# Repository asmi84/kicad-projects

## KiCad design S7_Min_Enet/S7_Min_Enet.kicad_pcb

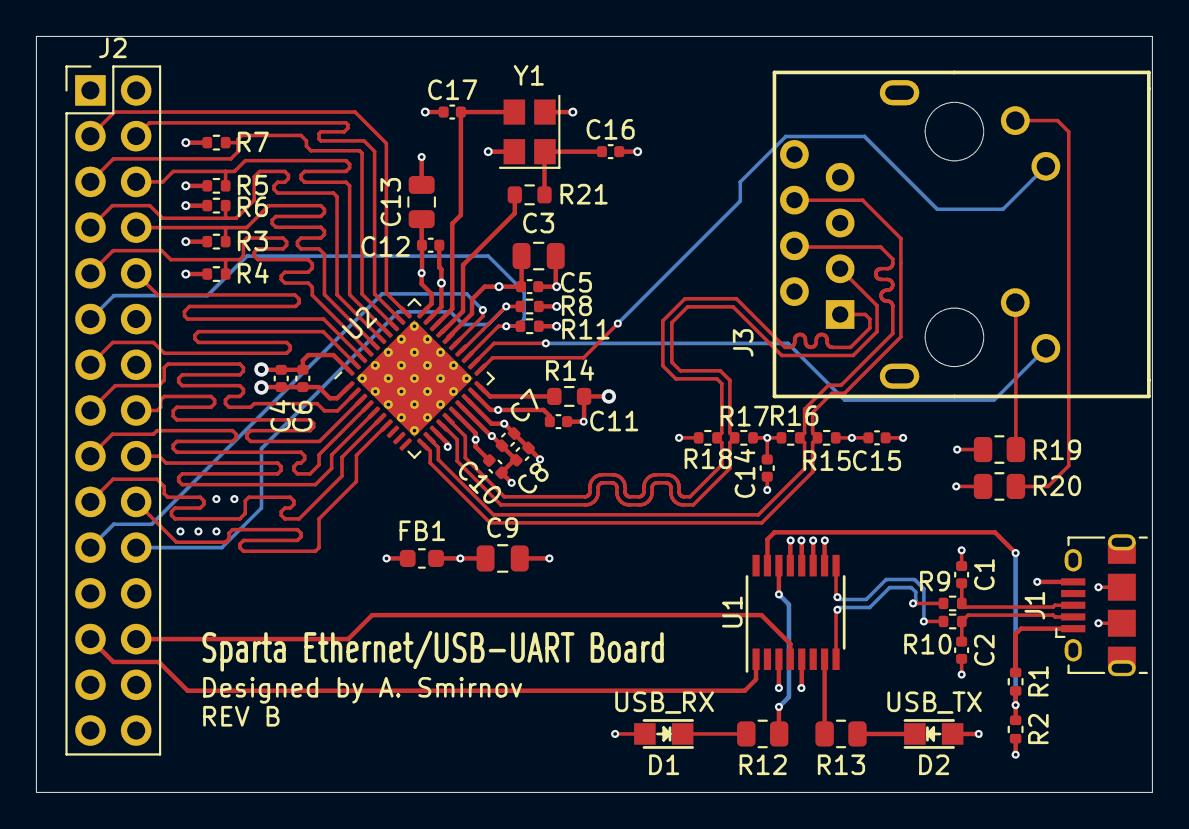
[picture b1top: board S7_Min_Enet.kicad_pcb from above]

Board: 4 copper layers, 62.0 x 42.0 mm, 47 parts (0 on the bottom side), 46 nets.

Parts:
C1, C2: 47pF; C_0402_1005Metric
C3, C9, C13: 10uF; C_0805_2012Metric
C4, C8: 1uF; C_0402_1005Metric
C5, C6, C7, C10, C11, C12, C14, C15: 0.1uF; C_0402_1005Metric
C16, C17: 33pF; C_0402_1005Metric
D1: USB_RX; LED_0805
D2: USB_TX; LED_0805
FB1: 600R; L_0603_1608Metric
J1: USB_B_Micro; USB_Micro-B_Amphenol_10118194_Horizontal
J2: Conn_02x15_Odd_Even; PinHeader_2x15_P2.54mm_Vertical
J3: J1B1211CCD
R1: 4.75K; R_0402_1005Metric
R2: 10K; R_0402_1005Metric
R3, R4, R5, R6: DNP; R_0402_1005Metric
R7, R8, R11: 2.2K; R_0402_1005Metric
R9, R10: 27; R_0402_1005Metric
R12, R13: 680; R_0805_2012Metric
R14: 4.87K; R_0603_1608Metric
R15, R16, R17, R18: 49.9; R_0402_1005Metric
R19, R20: 330; R_0805_2012Metric
R21: 0; R_0603_1608Metric
U1: FT230XS; SSOP-16_3.9x4.9mm_P0.635mm
U2: DP83848J; QFN-40-1EP_6x6mm_P0.5mm_EP4.6x4.6mm_ThermalVias
Y1: 25MHz; Crystal_SMD_3225-4Pin_3.2x2.5mm

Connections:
+3.3VA: C7.1, C8.1, C9.1, C14.1, C15.1, FB1.1, J3.2, J3.5, R15.2, R16.2, R17.2, R18.2, R19.1, R20.1, U2.18
+3V3: C3.1, C4.1, C5.1, C6.1, D1.2, D2.2, FB1.2, J2.1, J2.27, R3.2, R4.2, R5.2, R6.2, R7.2, R8.2, R11.2, U1.3, U1.10, U1.11, U1.12, U2.1, U2.26
/ETH_COL: J2.7, R6.1, U2.35
/ETH_CRS: J2.5, R7.1, U2.33
/ETH_MDC: J2.21, U2.25
/ETH_MDIO: J2.22, R8.1, U2.24
/ETH_RX+: J3.4, R16.1, U2.12
/ETH_RX-: J3.6, R15.1, U2.11
/ETH_RXD0: J2.8, R3.1, U2.36
/ETH_RXD1: J2.9, R4.1, U2.37
/ETH_RXD2: J2.10, U2.38
/ETH_RXD3: J2.13, U2.39
/ETH_RXERR: J2.6, R5.1, U2.34
/ETH_RX_CLK: J2.3, U2.31
/ETH_RX_DV: J2.4, U2.32
/ETH_TX+: J3.1, R18.1, U2.15
/ETH_TX-: J3.3, R17.1, U2.14
/ETH_TXD0: J2.17, U2.4
/ETH_TXD1: J2.18, U2.5
/ETH_TXD2: J2.19, U2.6
/ETH_TXD3: J2.20, U2.7
/ETH_TX_CLK: J2.15, U2.2
/ETH_TX_EN: J2.16, U2.3
/ETH_X1: C17.1, U2.28, Y1.3
/ETH_X2: R21.2, U2.27
/LED_LINK: J3.9, U2.22
/LED_SPD: J3.11, U2.21
/UART_RX: J2.26, U1.4
/UART_TX: J2.25, U1.1
/USB+: R9.1, U1.8
/USB-: R10.1, U1.9
/USB_J+: C1.1, J1.3, R9.2
/USB_J-: C2.1, J1.2, R10.2
/USB_VBUS_SENSE: R1.1, R2.2, U1.15
/~ETH_RST: J2.11, R11.1, U2.23
GND: C1.2, C2.2, C3.2, C4.2, C5.2, C6.2, C7.2, C8.2, C9.2, C10.2, C11.2, C12.2, C13.2, C14.2, C15.2, C16.1, C17.2, J1.5, J1.6, J2.2, J2.28, J2.30, J3.8, J3.S1, J3.S2, R2.1, R14.1, U1.5, U1.13, U2.13, U2.17, U2.29, U2.40, U2.41, Y1.2, Y1.4
unnamed: C10.1, C11.1, C12.1, C13.1, U2.16, U2.19, U2.30
unnamed: C16.2, R21.1, Y1.1
unnamed: D1.1, R12.1
unnamed: D2.1, R13.1
unnamed: J1.1, R1.2
unnamed: J3.10, R19.2
unnamed: J3.12, R20.2
unnamed: R12.2, U1.14
unnamed: R13.2, U1.7
unnamed: R14.2, U2.20

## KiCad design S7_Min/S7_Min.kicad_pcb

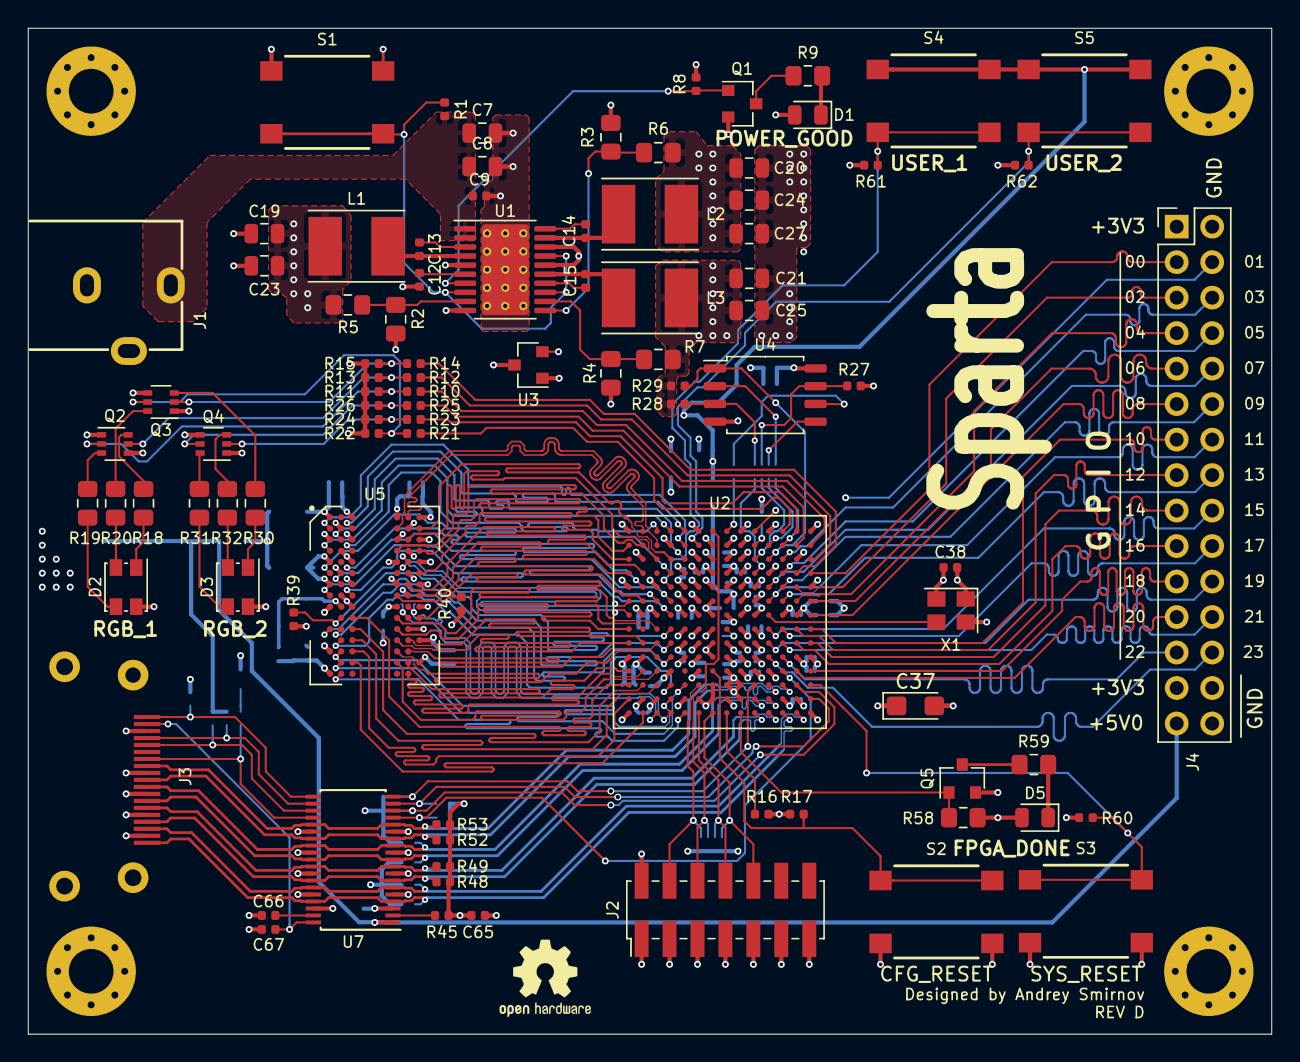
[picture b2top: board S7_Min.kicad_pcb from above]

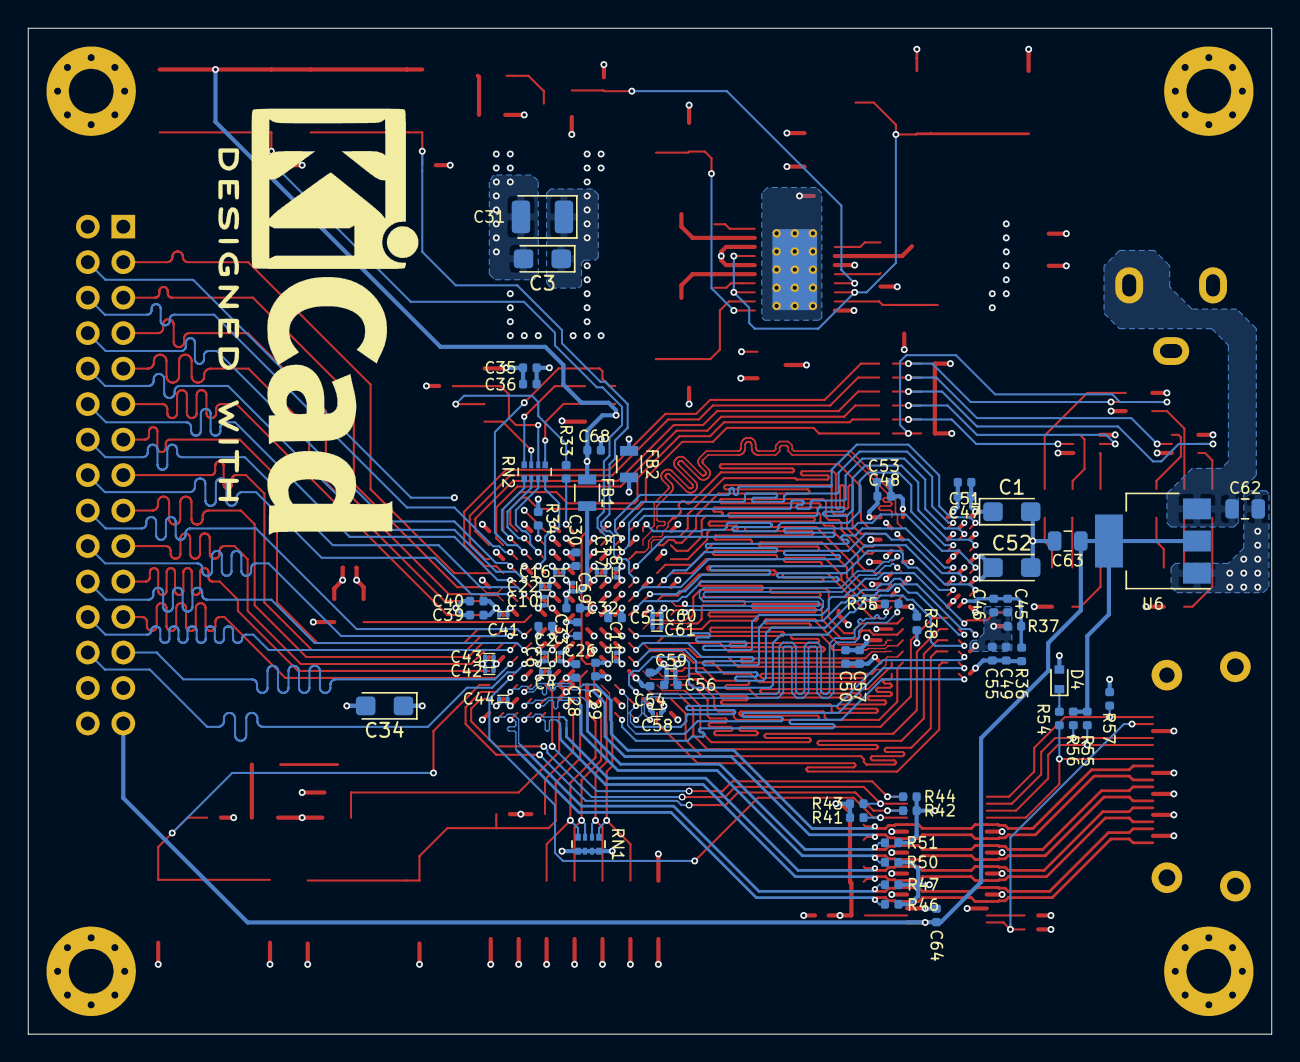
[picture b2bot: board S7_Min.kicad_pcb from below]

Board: 4 copper layers, 89.0 x 72.0 mm, 169 parts (74 on the bottom side), 164 nets.

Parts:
C1, C3, C34, C37, C52: 47 uF; CP_EIA-3216-18_Kemet-A
C2, C5, C28, C29, C30, C39, C40, C54, C56, C68: 4.7 uF; C_0402_1005Metric
C4, C6, C10, C11, C16, C17, C18, C22, C26, C41, C42, C43, C44, C58, C59, C60, C61, C69: 0.47 uF; C_0201_0603Metric
C7, C8, C62: 10 uF; C_0805_2012Metric
C9, C13, C14, C15, C32, C33, C35, C38, C45, C47, C48, C49, C50, C64, C65, C66, C67: 0.1 uF; C_0402_1005Metric
C12, C36, C51, C53, C55, C57: 1 uF; C_0402_1005Metric
C19, C20, C21, C23, C24, C25, C27, C63: 22 uF; C_0805_2012Metric
C31: 100 uF; CP_EIA-3528-15_AVX-H
C46: 10 nF; C_0402_1005Metric
D1: POWER_GOOD; LED_0805_2012Metric
D2, D3: LED_RAGB; LED_Kingbright_AAA3528ESGCT
D4: BAS16XV2T1G; D_SOD-523
D5: FPGA_DONE; LED_0805_2012Metric
FB1, FB2: 600R; L_0805
H1, H2, H3, H4: MountingHole_Pad; MountingHole_3.2mm_M3_Pad_Via
J1: Barrel_Jack_Switch; PJ_102B
J2: XILINX_JTAG; PinHeader_2x07_P2.00mm_Vertical_SMD
J3: HDMI_A; hdmi_type_a_10029449-111RLF
J4: Conn_02x15_Odd_Even; PinHeader_2x15_P2.54mm_Vertical
L1, L2, L3: 2.2 uH; L_Taiyo-Yuden_NR-50xx_HandSoldering
Q1, Q5: DMN2020L; SOT-23
Q2, Q3, Q4: DMN63D8LDW; SOT-363_SC-70-6
R1, R8, R44: 100K; R_0402_1005Metric
R2, R3, R4: 2.2K; R_0805_2012Metric_Pad1.15x1.40mm_HandSolder
R5: 3.0K; R_0805_2012Metric_Pad1.15x1.40mm_HandSolder
R6, R9, R18, R30, R59: 680; R_0805_2012Metric_Pad1.15x1.40mm_HandSolder
R7: 7.36K; R_0805_2012Metric_Pad1.15x1.40mm_HandSolder
R10, R12, R14, R21, R23, R25, R55, R56: 2.2K; R_0402_1005Metric
R11, R13, R15, R22, R24, R26, R45, R57: 10K; R_0402_1005Metric
R16, R17, R27, R28, R29, R34, R38, R39, R40, R60, R61, R62: 4.75K; R_0402_1005Metric
R19, R20, R31, R32, R58: 330; R_0805_2012Metric_Pad1.15x1.40mm_HandSolder
R33, R46, R47, R48, R49, R50, R51, R52, R53: 49.9; R_0402_1005Metric
R35: 100; R_0402_1005Metric
R36, R37: 1.0K; R_0402_1005Metric
R41, R42, R43: 47K; R_0402_1005Metric
R54: 27K; R_0402_1005Metric
RN1: 10K; R_Array_Convex_4x0402
RN2: 49.9; R_Array_Convex_4x0402
S1: PWR_OFF; B3FS_1010P
S2: CFG_RESET; B3FS_1010P
S3: SYS_RESET; B3FS_1010P
S4: USER_1; B3FS_1010P
S5: USER_2; B3FS_1010P
U1: TPS65581; HTSSOP-20-1EP_4.4x6.5mm_P0.65mm_EP3.4x6.5mm_Mask2.75x3.43mm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
U2: XC7S50-FTGB196; Xilinx_FTGB196
U3: REF3012; SOT-23
U4: QSPI_Flash_SOIC8; SOIC-8_5.275x5.275mm_P1.27mm
U5: MT47H128M16XX; BGA-84_9x15_9.0x12.5mm
U6: AZ1117-5.0; SOT-223-3_TabPin2
U7: TPD12S521; TSSOP-38_4.4x9.7mm_P0.5mm
X1: DSC61XX; Oscillator_SMD_Abracon_ASE-4Pin_3.2x2.5mm

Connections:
+1V0: C3.1, C5.1, C11.1, C16.1, C17.1, C18.1, C20.1, C22.1, C24.1, C26.1, C27.1, C28.1, C29.1, C30.1, C31.1, L2.2, R6.1, U2.D6, U2.D8, U2.E5, U2.E7, U2.E9, U2.F6, U2.G5, U2.G9, U2.H6, U2.J5, U2.J9, U2.K6, U2.K8
+1V8: C1.1, C2.1, C4.1, C6.1, C10.1, C19.1, C23.1, C47.1, C48.1, C49.1, C50.1, C51.1, C52.1, C53.1, C54.1, C55.1, C56.1, C57.1, C58.1, C59.1, C60.1, C61.1, C68.1, FB1.2, L1.2, R5.1, R36.2, S4.1, S4.2, S5.1, S5.2, U2.F10, U2.G2, U2.H10, U2.K2, U2.K10, U2.L9, U2.N2, U5.A1, U5.A9, U5.C1, U5.C3, U5.C7, U5.C9, U5.E1, U5.E9, U5.G1, U5.G3, U5.G7, U5.G9, U5.J1, U5.J9, U5.M9, U5.R1
+1V8A: C32.1, C69.1, FB1.1, U2.F8
+3V3: C21.1, C25.1, C34.1, C35.1, C36.1, C37.1, C38.1, C39.1, C40.1, C41.1, C42.1, C43.1, C44.1, C65.1, D1.2, D2.2, D3.2, D4.2, D5.2, J2.2, J4.1, J4.27, L3.2, R7.1, R8.2, R16.2, R17.2, R27.2, R28.2, R29.2, R34.1, R41.1, R42.1, R43.1, R44.1, R45.2, R46.1, R47.1, R48.1, R49.1, R50.1, R51.1, R52.1, R53.1, R58.2, R60.1, RN1.5, RN1.6, RN1.7, RN1.8, U2.G13, U2.K13, U2.M7, U2.N6, U2.N7, U2.N8, U2.N13, U3.1, U4.8, X1.1, X1.4
+5V: C63.1, C64.1, J4.29, R55.2, R56.2, U6.2, U7.1
+12V: C7.1, C8.1, C9.1, C62.2, J1.1, R1.2, U1.1, U1.2, U6.3
/Bank0_14/FPGA_DONE: Q5.1, R58.1, U2.P9
/Bank0_14/FPGA_PUDC: R34.2, U2.B10
/Bank0_14/INIT_B: R16.1, U2.P8
/Bank0_14/JTAG_TCK: J2.6, RN1.2, U2.A7
/Bank0_14/JTAG_TDI: J2.10, RN1.4, U2.P7
/Bank0_14/JTAG_TDO: J2.8, RN1.3, U2.P6
/Bank0_14/JTAG_TMS: J2.4, RN1.1, U2.M6
/Bank0_14/PROGRAM_B: R17.1, S2.1, S2.2, U2.L7
/Bank0_14/RGB1_B: R14.2, U2.D13
/Bank0_14/RGB1_G: R12.2, U2.C14
/Bank0_14/RGB1_R: R10.2, U2.B14
/Bank0_14/RGB2_B: R25.2, U2.B13
/Bank0_14/RGB2_G: R23.2, U2.A13
/Bank0_14/RGB2_R: R21.2, U2.A12
/Bank0_14/SPI_CS: R29.1, U2.C11, U4.1
/Bank0_14/SPI_DQ0: RN2.3, U4.5
/Bank0_14/SPI_DQ1: RN2.4, U4.2
/Bank0_14/SPI_DQ2: R28.1, RN2.1, U4.3
/Bank0_14/SPI_DQ3: R27.1, RN2.2, U4.7
/Bank0_14/SPI_F_DQ0: RN2.6, U2.B11
/Bank0_14/SPI_F_DQ1: RN2.5, U2.B12
/Bank0_14/SPI_F_DQ2: RN2.8, U2.D10
/Bank0_14/SPI_F_DQ3: RN2.7, U2.C10
/Bank0_14/SPI_F_SCLK: R33.1, U2.A8
/Bank0_14/SPI_SCLK: R33.2, U4.6
/Bank0_14/SYSCLK: U2.G11, X1.3
/Bank0_14/SYSRESET: R60.2, S3.1, S3.2, U2.M14
/Bank34/DDR2_A0: U2.J2, U5.M8
/Bank34/DDR2_A1: U2.M3, U5.M3
/Bank34/DDR2_A2: U2.J1, U5.M7
/Bank34/DDR2_A3: U2.N4, U5.N2
/Bank34/DDR2_A4: U2.J3, U5.N8
/Bank34/DDR2_A5: U2.N1, U5.N3
/Bank34/DDR2_A6: U2.K3, U5.N7
/Bank34/DDR2_A7: U2.M5, U5.P2
/Bank34/DDR2_A8: U2.L1, U5.P8
/Bank34/DDR2_A9: U2.P2, U5.P3
/Bank34/DDR2_A10: U2.M4, U5.M2
/Bank34/DDR2_A11: U2.L3, U5.P7
/Bank34/DDR2_A12: U2.P5, U5.R2
/Bank34/DDR2_A13: U2.L2, U5.R8
/Bank34/DDR2_BA0: U2.K4, U5.L2
/Bank34/DDR2_BA1: U2.M2, U5.L3
/Bank34/DDR2_BA2: U2.J4, U5.L1
/Bank34/DDR2_CAS: U2.H1, U5.L7
/Bank34/DDR2_CK+: R35.1, U2.P4, U5.J8
/Bank34/DDR2_CK-: R35.2, U2.P3, U5.K8
/Bank34/DDR2_CKE: R39.2, U2.H4, U5.K2
/Bank34/DDR2_DM0: U2.E2, U5.F3
/Bank34/DDR2_DM1: U2.A5, U5.B3
/Bank34/DDR2_DQ0: U2.D2, U5.G8
/Bank34/DDR2_DQ1: U2.F4, U5.G2
/Bank34/DDR2_DQ2: U2.F2, U5.H7
/Bank34/DDR2_DQ3: U2.G4, U5.H3
/Bank34/DDR2_DQ4: U2.F3, U5.H1
/Bank34/DDR2_DQ5: U2.D1, U5.H9
/Bank34/DDR2_DQ6: U2.D4, U5.F1
/Bank34/DDR2_DQ7: U2.C1, U5.F9
/Bank34/DDR2_DQ8: U2.C3, U5.C8
/Bank34/DDR2_DQ9: U2.C5, U5.C2
/Bank34/DDR2_DQ10: U2.B2, U5.D7
/Bank34/DDR2_DQ11: U2.A3, U5.D3
/Bank34/DDR2_DQ12: U2.A4, U5.D1
/Bank34/DDR2_DQ13: U2.B1, U5.D9
/Bank34/DDR2_DQ14: U2.B5, U5.B1
/Bank34/DDR2_DQ15: U2.C4, U5.B9
/Bank34/DDR2_DQS0+: U2.G1, U5.F7
/Bank34/DDR2_DQS0-: U2.F1, U5.E8
/Bank34/DDR2_DQS1+: U2.B3, U5.B7
/Bank34/DDR2_DQS1-: U2.A2, U5.A8
/Bank34/DDR2_ODT: R40.2, U2.H3, U5.K9
/Bank34/DDR2_RAS: U2.H2, U5.K7
/Bank34/DDR2_WE: U2.M1, U5.K3
/Bank34/USER_1: R61.1, S4.3, S4.4, U2.E4
/Bank34/USER_2: R62.1, S5.3, S5.4, U2.B6
/Externals/HDMI_C_5V: C67.2, J3.18, U7.38
/Externals/HDMI_C_CEC: J3.13, R54.1, U7.23
/Externals/HDMI_C_HPD: J3.19, R57.1, U7.20
/Externals/HDMI_C_SCL: J3.15, R55.1, U7.22
/Externals/HDMI_C_SDA: J3.16, R56.1, U7.21
/Power/PGOOD: Q1.1, R8.1, U1.7
/Power/SW1: C13.1, L1.1, U1.4
/Power/SW2: C14.1, L2.1, U1.19
/Power/SW3: C15.1, L3.1, U1.15
ADC_REF: C33.1, U2.H8, U3.2
GND: C1.2, C2.2, C3.2, C4.2, C5.2, C6.2, C7.2, C8.2, C9.2, C10.2, C11.2, C12.2, C16.2, C17.2, C18.2, C19.2, C20.2, C21.2, C22.2, C23.2, C24.2, C25.2, C26.2, C27.2, C28.2, C29.2, C30.2, C31.2, C34.2, C35.2, C36.2, C37.2, C38.2, C39.2, C40.2, C41.2, C42.2, C43.2, C44.2, C45.2, C46.2, C47.2, C48.2, C49.2, C50.2, C51.2, C52.2, C53.2, C54.2, C55.2, C56.2, C57.2, C58.2, C59.2, C60.2, C61.2, C62.1, C63.2, C64.2, C65.2, C66.1, C67.1, C68.2, C69.2, FB2.2, H1.1, H2.1, H3.1, H4.1, J1.2, J2.1, J2.3, J2.5, J2.7, J2.9, J2.11, J2.13, J3.2, J3.5, J3.8, J3.11, J3.17, J3.SH, J4.2, J4.28, J4.30, Q1.2, Q2.1, Q2.4, Q3.1, Q3.4, Q4.1, Q4.4, Q5.2, R2.2, R3.2, R4.2, R11.2, R13.2, R15.2, R22.2, R24.2, R26.2, R37.1, R38.1, R39.1, R40.1, R57.2, R61.2, R62.2, S1.1, S1.2, S2.3, S2.4, S3.3, S3.4, U1.5, U1.10, U1.16, U1.18, U1.21, U2.A1, U2.A6, U2.A9, U2.A11, U2.A14, U2.B4, U2.B7, U2.B8, U2.B9, U2.C2, U2.C6, U2.C7, U2.C8, U2.C9, U2.C13, U2.D5, U2.D7, U2.D9, U2.D11, U2.E1, U2.E3, U2.E6, U2.E8, U2.E10, U2.E14, U2.F5, U2.F9, U2.G3, U2.G6, U2.G10, U2.G12, U2.H5, U2.H9, U2.J6, U2.J7, U2.J8, U2.J10, U2.K1, U2.K5, U2.K7, U2.K9, U2.K14, U2.L4, U2.L6, U2.L8, U2.L10, U2.L11, U2.M8, U2.M9, U2.N3, U2.N5, U2.N9, U2.N12, U2.P1, U2.P14, U3.3, U4.4, U5.A3, U5.A7, U5.B2, U5.B8, U5.D2, U5.D8, U5.E3, U5.E7, U5.F2, U5.F8, U5.H2, U5.H8, U5.J3, U5.J7, U5.N1, U5.P9, U6.1, U7.3, U7.5, U7.8, U7.11, U7.14, U7.25, U7.28, U7.31, U7.34, U7.36, X1.2
GNDA: C32.2, C33.2, FB2.1, U2.F7, U2.G7, U2.G8, U2.H7
GPIO_0: J4.3, U2.D14
GPIO_1: J4.4, U2.A10
GPIO_2: J4.5, U2.E13
GPIO_3: J4.6, U2.C12
GPIO_4: J4.7, U2.F13
GPIO_5: J4.8, U2.D12
GPIO_6: J4.9, U2.F14
GPIO_7: J4.10, U2.E11
GPIO_8: J4.11, U2.G14
GPIO_9: J4.12, U2.E12
GPIO_10: J4.13, U2.H14
GPIO_11: J4.14, U2.F11
GPIO_12: J4.15, U2.H13
GPIO_13: J4.16, U2.F12
GPIO_14: J4.17, U2.J14
GPIO_15: J4.18, U2.H11
GPIO_16: J4.19, U2.J13
GPIO_17: J4.20, U2.H12
GPIO_18: J4.21, U2.L14
GPIO_19: J4.22, U2.J11
GPIO_20: J4.23, U2.L13
GPIO_21: J4.24, U2.J12
GPIO_22: J4.25, U2.K12
GPIO_23: J4.26, U2.K11
HDMI_CEC: R41.2, U2.L12, U7.16
HDMI_CLK+: J3.10, R52.2, U2.M11, U7.13, U7.26
HDMI_CLK-: J3.12, R53.2, U2.M12, U7.15, U7.24
HDMI_D0+: J3.7, R50.2, U2.N10, U7.10, U7.29
HDMI_D0-: J3.9, R51.2, U2.N11, U7.12, U7.27
HDMI_D1+: J3.4, R48.2, U2.P10, U7.7, U7.32
HDMI_D1-: J3.6, R49.2, U2.P11, U7.9, U7.30
HDMI_D2+: J3.1, R46.2, U2.P12, U7.4, U7.35
HDMI_D2-: J3.3, R47.2, U2.P13, U7.6, U7.33
HDMI_HPD: R44.2, U2.M10, U7.19
HDMI_SCL: R42.2, U2.M13, U7.17
HDMI_SDA: R43.2, U2.N14, U7.18
unnamed: C12.1, U1.6
unnamed: C13.2, U1.3
unnamed: C14.2, U1.20
unnamed: C15.2, U1.14
unnamed: C45.1, C46.1, R36.1, R37.2, U5.J2
unnamed: C66.2, U7.37
unnamed: D1.1, R9.2
unnamed: D2.1, R18.1
unnamed: D2.3, R19.1
unnamed: D2.4, R20.1
unnamed: D3.1, R30.1
unnamed: D3.3, R31.1
unnamed: D3.4, R32.1
unnamed: D4.1, R54.2
unnamed: D5.1, R59.2
unnamed: Q1.3, R9.1
unnamed: Q2.2, R10.1, R11.1
unnamed: Q2.3, R19.2
unnamed: Q2.5, R12.1, R13.1
unnamed: Q2.6, R18.2
unnamed: Q3.2, R14.1, R15.1
unnamed: Q3.3, R30.2
unnamed: Q3.5, R21.1, R22.1
unnamed: Q3.6, R20.2
unnamed: Q4.2, R23.1, R24.1
unnamed: Q4.3, R32.2
unnamed: Q4.5, R25.1, R26.1
unnamed: Q4.6, R31.2
unnamed: Q5.3, R59.1
unnamed: R1.1, S1.3, S1.4, U1.8, U1.13, U1.17
unnamed: R2.1, R5.2, U1.9
unnamed: R3.1, R6.2, U1.11
unnamed: R4.1, R7.2, U1.12
unnamed: R38.2, U5.L8
unnamed: R45.1, U7.2

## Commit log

2019-11-04 DDR2 layout WIP
2019-11-04 3D models setup
2019-11-04 updated footprints from library
2019-11-04 more DDR2 WIP
2019-11-04 DDR2 interface mostly completed
2019-11-04 updated board to user custom footprint for 0201 caps
2019-11-05 updated board with new 0201 footprint
2019-11-05 added HDMI TX into schematics
2019-11-06 changed HDMI connector footprint to use custom one
2019-11-06 connected HDMI connector's shield to GND
2019-11-08 added MIG pinout file
2019-12-10 made library references relative to the project directory (thanks Codealot!)
2019-12-10 changed package of 2 ADC capacitors to 0402 from 0201 to eliminate a BOM line
2019-12-13 Layout is completed, DRC passed, first pass on a silk layers
2019-12-13 Silk ready
2019-12-13 Replaces 47 uF caps footprint to polarized (tantalum)
2019-12-13 REV A Ordered
2019-12-13 Added schematic PDF
2019-12-13 added silkscreen labels to buttons "CFG_RESET" and "SYS_RESET"
2019-12-24 fixed the layout after adding missing PAD pin to TPS65581 symbol :facepalm: added some exposed ground on the bottom side to improve thermals.
2019-12-28 REV B Gerbers added
2020-01-27 REV C: - fixed power disable button connections (:facepalm:) - "FPGA_DONE" and "POWER_GOOD" LEDs were connected backwards
2020-01-27 updated schematics PDF, added assembly document
2020-12-07 added s7 min enet addon board
2020-12-10 changed path to a custom library to relative
2020-12-16 completed rev A for Ethernet board
2020-12-16 matched length of all GPIO traces to 40.7±0.1 mm
2020-12-16 Added gerbers for rev D main board and rev A ethernet board, schematic PDF for ethernet
2020-12-16 removed backup file
2020-12-24 added assembly file
2020-12-25 fixed assembly file
2020-12-25 revision B - fixed USB connection
2021-01-11 made some resistors DNP, updated schematics and assembly docs
